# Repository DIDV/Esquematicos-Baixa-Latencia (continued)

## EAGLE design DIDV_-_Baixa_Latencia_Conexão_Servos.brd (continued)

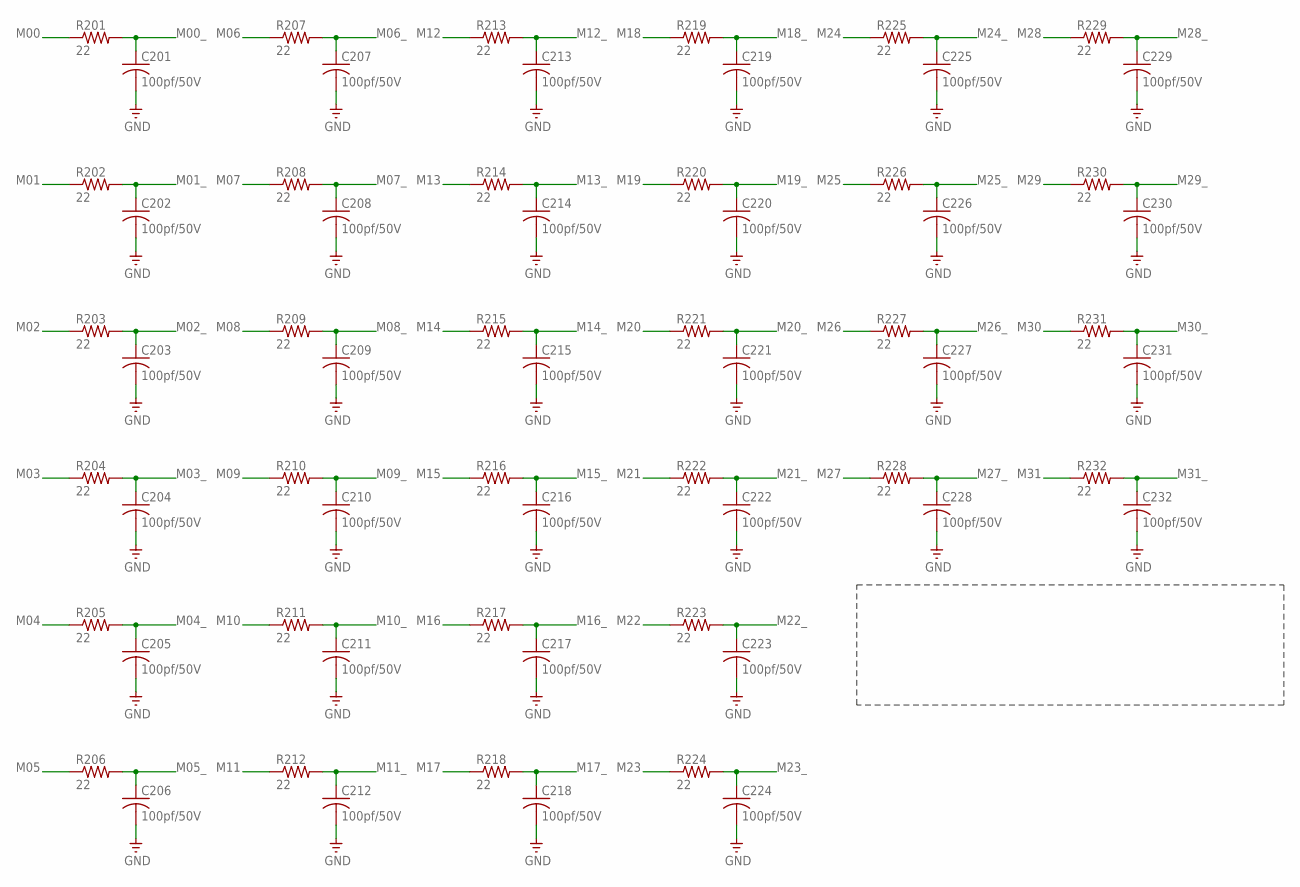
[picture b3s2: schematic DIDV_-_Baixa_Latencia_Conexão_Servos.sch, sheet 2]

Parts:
C201, C202, C203, C204, C205, C206, C207, C208, C209, C210, C211, C212, C213, C214, C215, C216, C217, C218, C219, C220, C221, C222, C223, C224, C225, C226, C227, C228, C229, C230, C231, C232: 100pf/50V; C0603
R201, R202, R203, R204, R205, R206, R207, R208, R209, R210, R211, R212, R213, R214, R215, R216, R217, R218, R219, R220, R221, R222, R223, R224, R225, R226, R227, R228, R229, R230, R231, R232: 22; R0603

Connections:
GND: C201.2, C202.2, C203.2, C204.2, C205.2, C206.2, C207.2, C208.2, C209.2, C210.2, C211.2, C212.2, C213.2, C214.2, C215.2, C216.2, C217.2, C218.2, C219.2, C220.2, C221.2, C222.2, C223.2, C224.2, C225.2, C226.2, C227.2, C228.2, C229.2, C230.2, C231.2, C232.2; also elsewhere on the board
M00: R201.1; also elsewhere on the board
M00_: C201.1, R201.2; also elsewhere on the board
M01: R202.1; also elsewhere on the board
M01_: C202.1, R202.2; also elsewhere on the board
M02: R203.1; also elsewhere on the board
M02_: C203.1, R203.2; also elsewhere on the board
M03: R204.1; also elsewhere on the board
M03_: C204.1, R204.2; also elsewhere on the board
M04: R205.1; also elsewhere on the board
M04_: C205.1, R205.2; also elsewhere on the board
M05: R206.1; also elsewhere on the board
M05_: C206.1, R206.2; also elsewhere on the board
M06: R207.1; also elsewhere on the board
M06_: C207.1, R207.2; also elsewhere on the board
M07: R208.1; also elsewhere on the board
M07_: C208.1, R208.2; also elsewhere on the board
M08: R209.1; also elsewhere on the board
M08_: C209.1, R209.2; also elsewhere on the board
M09: R210.1; also elsewhere on the board
M09_: C210.1, R210.2; also elsewhere on the board
M10: R211.1; also elsewhere on the board
M10_: C211.1, R211.2; also elsewhere on the board
M11: R212.1; also elsewhere on the board
M11_: C212.1, R212.2; also elsewhere on the board
M12: R213.1; also elsewhere on the board
M12_: C213.1, R213.2; also elsewhere on the board
M13: R214.1; also elsewhere on the board
M13_: C214.1, R214.2; also elsewhere on the board
M14: R215.1; also elsewhere on the board
M14_: C215.1, R215.2; also elsewhere on the board
M15: R216.1; also elsewhere on the board
M15_: C216.1, R216.2; also elsewhere on the board
M16: R217.1; also elsewhere on the board
M16_: C217.1, R217.2; also elsewhere on the board
M17: R218.1; also elsewhere on the board
M17_: C218.1, R218.2; also elsewhere on the board
M18: R219.1; also elsewhere on the board
M18_: C219.1, R219.2; also elsewhere on the board
M19: R220.1; also elsewhere on the board
M19_: C220.1, R220.2; also elsewhere on the board
M20: R221.1; also elsewhere on the board
M20_: C221.1, R221.2; also elsewhere on the board
M21: R222.1; also elsewhere on the board
M21_: C222.1, R222.2; also elsewhere on the board
M22: R223.1; also elsewhere on the board
M22_: C223.1, R223.2; also elsewhere on the board
M23: R224.1; also elsewhere on the board
M23_: C224.1, R224.2; also elsewhere on the board
M24: R225.1; also elsewhere on the board
M24_: C225.1, R225.2; also elsewhere on the board
M25: R226.1; also elsewhere on the board
M25_: C226.1, R226.2; also elsewhere on the board
M26: R227.1; also elsewhere on the board
M26_: C227.1, R227.2; also elsewhere on the board
M27: R228.1; also elsewhere on the board
M27_: C228.1, R228.2; also elsewhere on the board
M28: R229.1; also elsewhere on the board
M28_: C229.1, R229.2; also elsewhere on the board
M29: R230.1; also elsewhere on the board
M29_: C230.1, R230.2; also elsewhere on the board
M30: R231.1; also elsewhere on the board
M30_: C231.1, R231.2; also elsewhere on the board
M31: R232.1; also elsewhere on the board
M31_: C232.1, R232.2; also elsewhere on the board

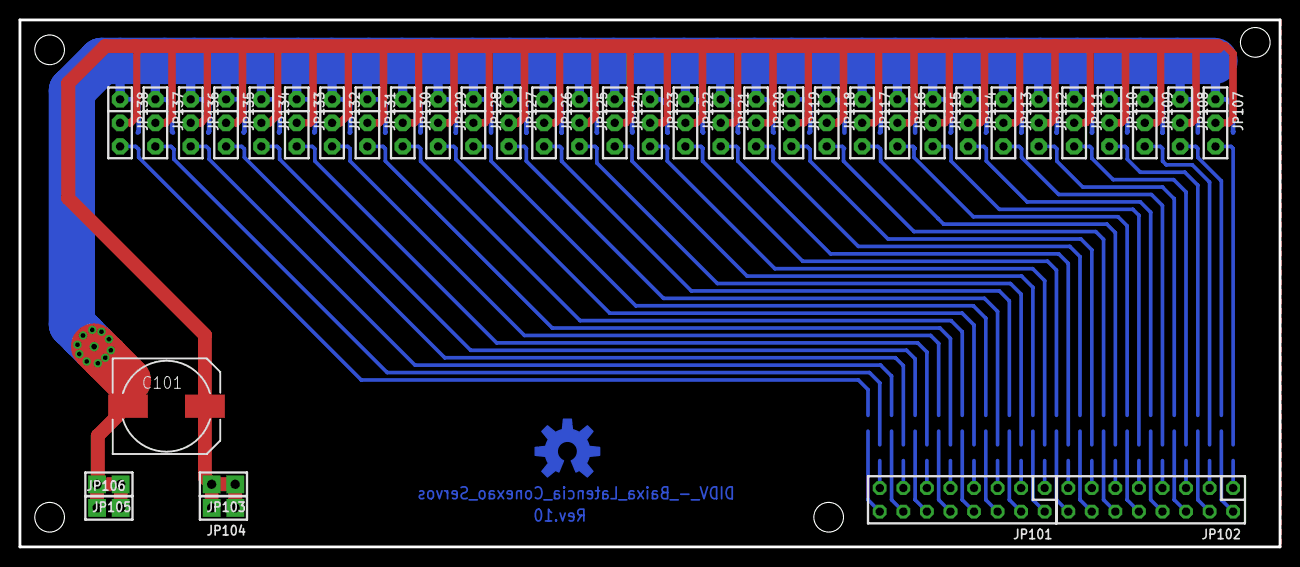
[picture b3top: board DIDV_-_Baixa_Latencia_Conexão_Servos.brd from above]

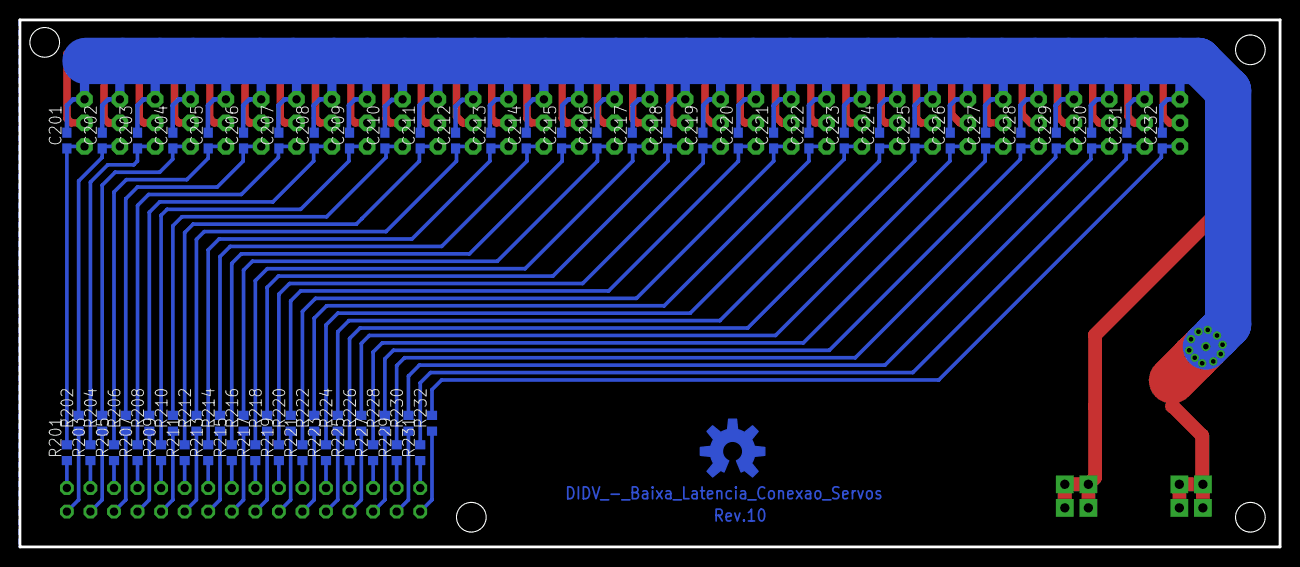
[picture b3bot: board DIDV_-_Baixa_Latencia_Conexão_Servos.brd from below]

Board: 2 copper layers, 135.9 x 56.8 mm, 104 parts (64 on the bottom side), 66 nets.

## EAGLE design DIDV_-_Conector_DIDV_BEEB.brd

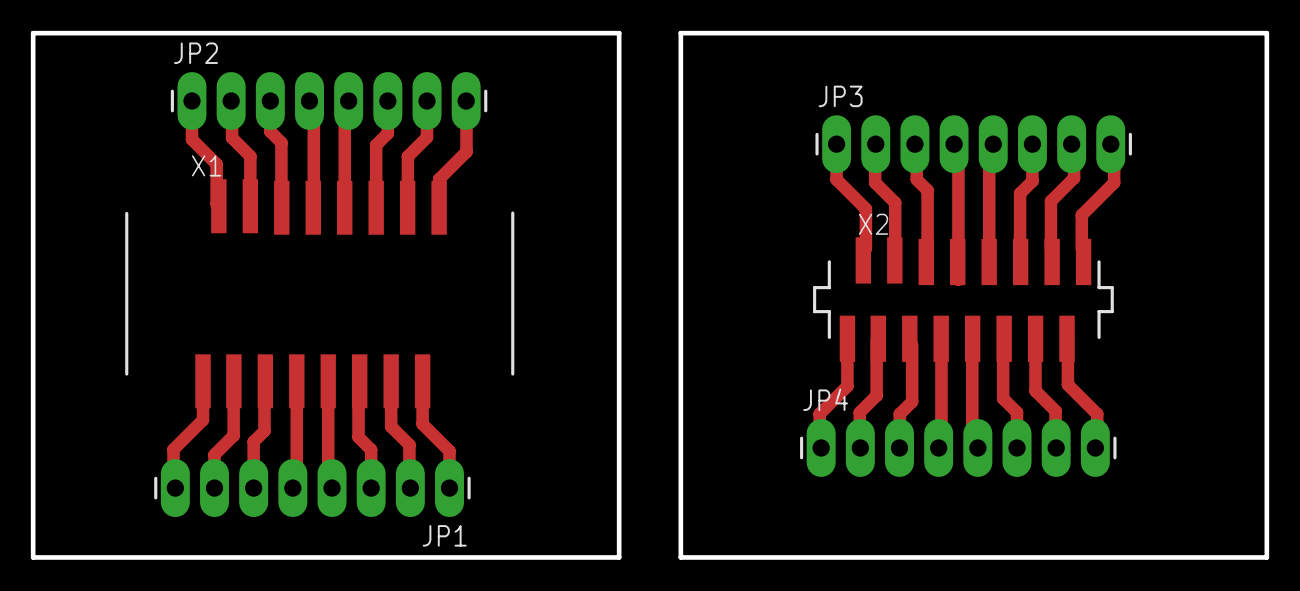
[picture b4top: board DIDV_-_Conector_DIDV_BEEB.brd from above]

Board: 2 copper layers, 80.0 x 34.0 mm, 6 parts (0 on the bottom side), 16 nets.

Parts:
JP1, JP2, JP3, JP4: 1X08_LONGPADS
X1, X2: SMDTOP16

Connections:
unnamed: JP1.8, X1.1
unnamed: JP1.1, X1.15
unnamed: JP1.7, X1.3
unnamed: JP1.6, X1.5
unnamed: JP1.5, X1.7
unnamed: JP1.2, X1.13
unnamed: JP1.3, X1.11
unnamed: JP1.4, X1.9
unnamed: JP2.7, X1.14
unnamed: JP2.6, X1.12
unnamed: JP2.5, X1.10
unnamed: JP2.2, X1.4
unnamed: JP2.3, X1.6
unnamed: JP2.4, X1.8
unnamed: JP2.1, X1.2
unnamed: JP2.8, X1.16

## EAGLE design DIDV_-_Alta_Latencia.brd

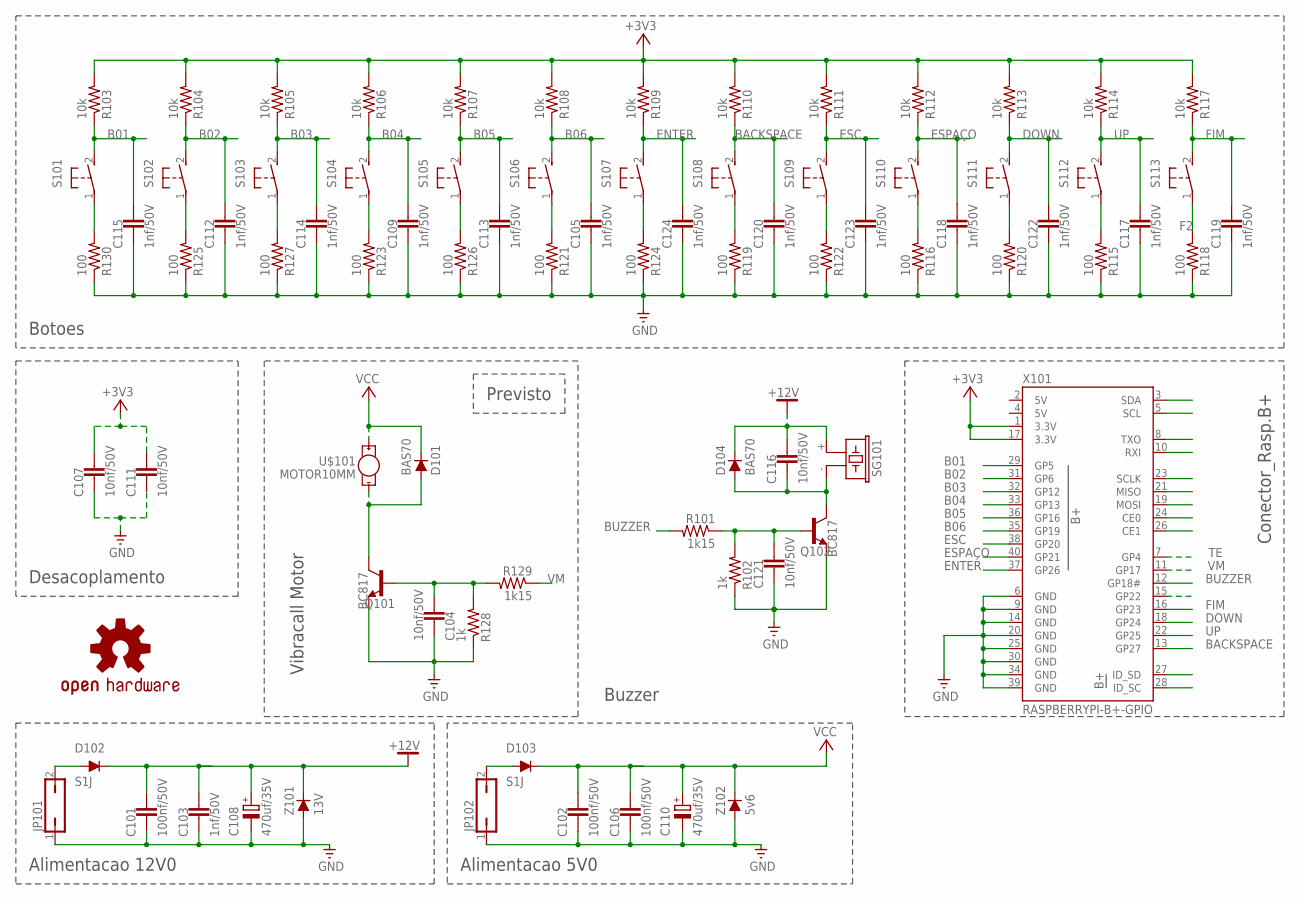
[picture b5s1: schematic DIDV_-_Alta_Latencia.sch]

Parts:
C101, C102, C106: 100nf/50V; C0805
C103: 1nf/50V; C0805
C104, C107, C111, C116, C121: 10nf/50V; C0603K
C105, C109, C112, C113, C114, C115, C117, C118, C119, C120, C122, C123, C124: 1nf/50V; C0603K
C108, C110: 470uf/35V; 140CLH-1014
D101, D104: BAS70; SOT23
D102, D103: S1J; DO214AC
JP101, JP102: JP1QY; JP1Y
LOGO101: OSHW-LOGOL; OSHW-LOGO-L
Q101, Q102: BC817; SOT23-BEC
R101, R129: 1k15; R0805
R102, R128: 1k; R0805
R103, R104, R105, R106, R107, R108, R109, R110, R111, R112, R113, R114, R117: 10k; R0603
R115, R116, R118, R119, R120, R121, R122, R123, R124, R125, R126, R127, R130: 100; R0603
S101, S102, S103, S104, S105, S106, S107, S108, S109, S110, S111, S112, S113: DTS-3
SG101: F/CM12P
U$101: MOTOR10MM; VIBE-MOTOR-10MM
X101: RASPBERRYPI-B+-GPIO; 2X20-SHROUDED
Z101: 13V; SOT23
Z102: 5v6; SOT23

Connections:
5V: X101.2 (5V), X101.4 (5V)
+3V3: C107.1, C111.1, R103.2, R104.2, R105.2, R106.2, R107.2, R108.2, R109.2, R110.2, R111.2, R112.2, R113.2, R114.2, R117.2, X101.1 (3.3V), X101.17 (3.3V)
+12V: C101.1, C103.1, C108.+, C116.1, D102.C, D104.3 (C), SG101.+ (1), Z101.3 (C)
B01: C115.1, R103.1, S101.2, X101.29 (GP5)
B02: C112.1, R104.1, S102.2, X101.31 (GP6)
B03: C114.1, R105.1, S103.2, X101.32 (GP12)
B04: C109.1, R106.1, S104.2, X101.33 (GP13)
B05: C113.1, R107.1, S105.2, X101.36 (GP16)
B06: C105.1, R108.1, S106.2, X101.35 (GP19)
BACKSPACE: C120.1, R110.1, S108.2, X101.13 (GP27)
BUZZER: R101.2, X101.12 (GP18#)
DOWN: C122.1, R113.1, S111.2, X101.18 (GP24)
ENTER: C124.1, R109.1, S107.2, X101.37 (GP26)
ESC: C123.1, R111.1, S109.2, X101.38 (GP20)
ESPAÇO: C118.1, R112.1, S110.2, X101.40 (GP21)
F2: R118.2, S113.1
FIM: C119.1, R117.1, S113.2, X101.16 (GP23)
GND: C101.2, C102.2, C103.2, C104.2, C105.2, C106.2, C107.2, C108.-, C109.2, C110.-, C111.2, C112.2, C113.2, C114.2, C115.2, C117.2, C118.2, C119.2, C120.2, C122.2, C123.2, C124.2, JP101.1, JP102.1, Q101.E, R115.1, R116.1, R118.1, R119.1, R120.1, R121.1, R122.1, R123.1, R124.1, R125.1, R126.1, R127.1, R128.1, R130.1, X101.6 (GND), X101.9 (GND), X101.14 (GND), X101.20 (GND), X101.25 (GND), X101.30 (GND), X101.34 (GND), X101.39 (GND), Z101.1 (A), Z102.1 (A)
unnamed: C116.2, D104.1 (A), Q102.C, SG101.- (2)
unnamed: C121.1, Q102.B, R101.1, R102.2
unnamed: R130.2, S101.1
unnamed: R121.2, S106.1
unnamed: R126.2, S105.1
unnamed: R123.2, S104.1
unnamed: R127.2, S103.1
unnamed: R125.2, S102.1
unnamed: R124.2, S107.1
unnamed: R115.2, S112.1
unnamed: R120.2, S111.1
unnamed: R116.2, S110.1
unnamed: R122.2, S109.1
unnamed: R119.2, S108.1
unnamed: C104.1, Q101.B, R128.2, R129.2
unnamed: D101.1 (A), Q101.C, U$101.-
unnamed: D102.A, JP101.2
unnamed: D103.A, JP102.2
unnamed: C121.2, Q102.E, R102.1
TE: X101.7 (GP4)
UP: C117.1, R114.1, S112.2, X101.22 (GP25)
VCC: C102.1, C106.1, C110.+, D101.3 (C), D103.C, U$101.+, Z102.3 (C)
VM: R129.1, X101.11 (GP17)

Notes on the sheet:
Buzzer
Botoes
Conector_Rasp.B+
Vibracall Motor
Previsto
Alimentacao 12V0
Alimentacao 5V0
Desacoplamento

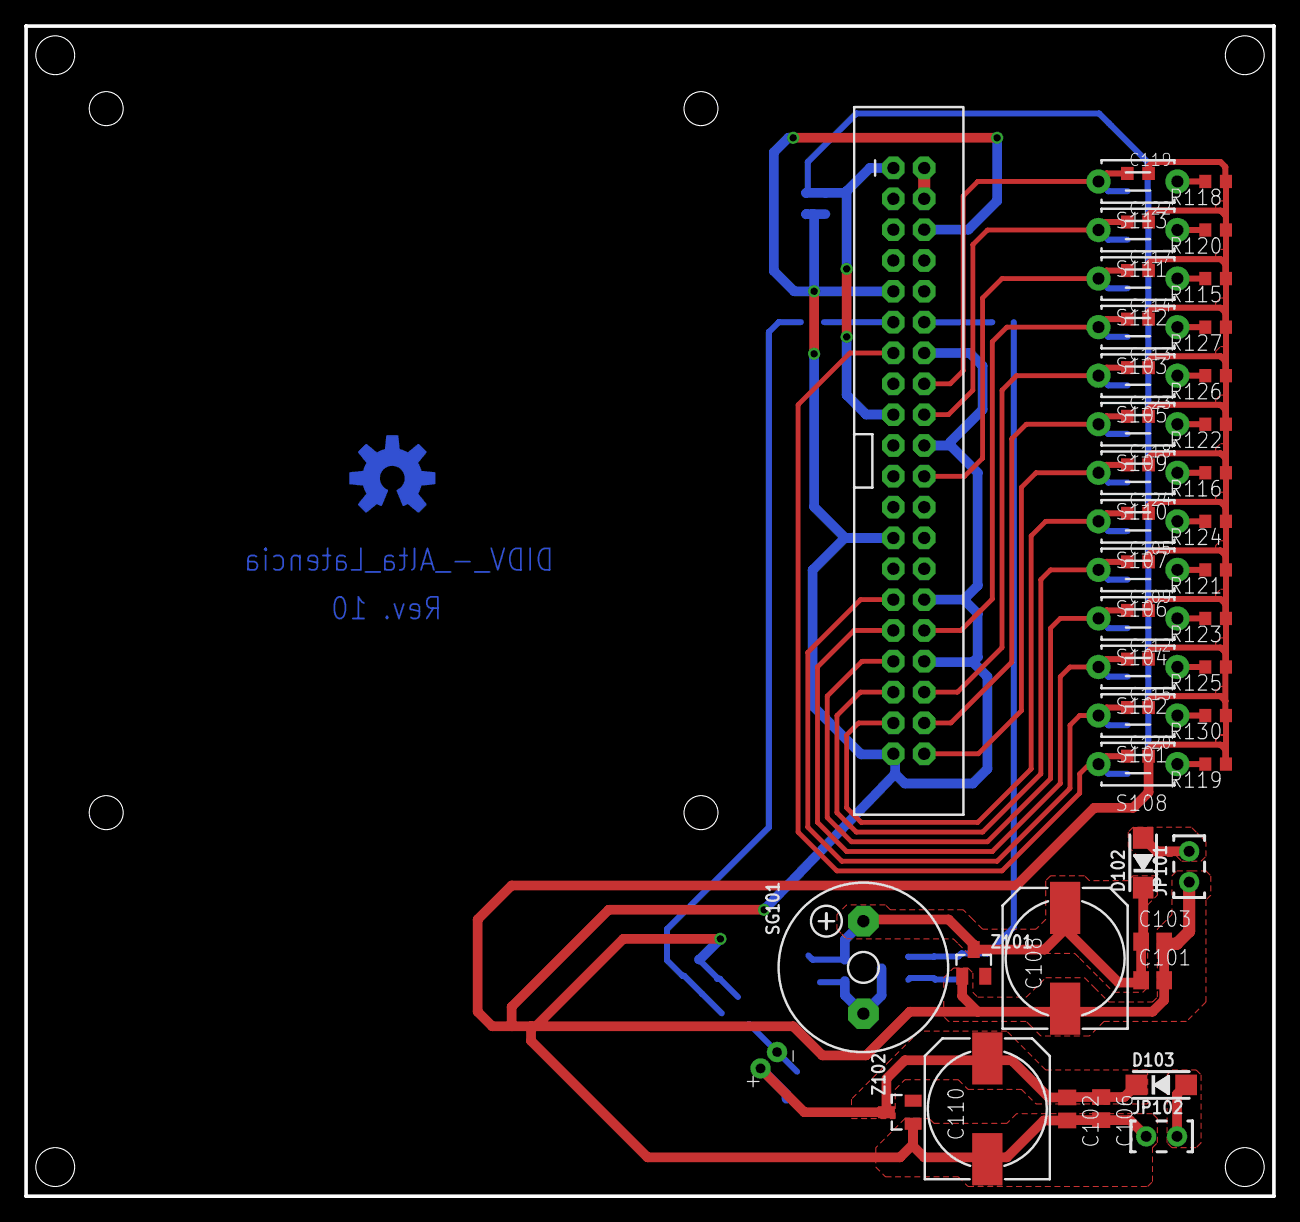
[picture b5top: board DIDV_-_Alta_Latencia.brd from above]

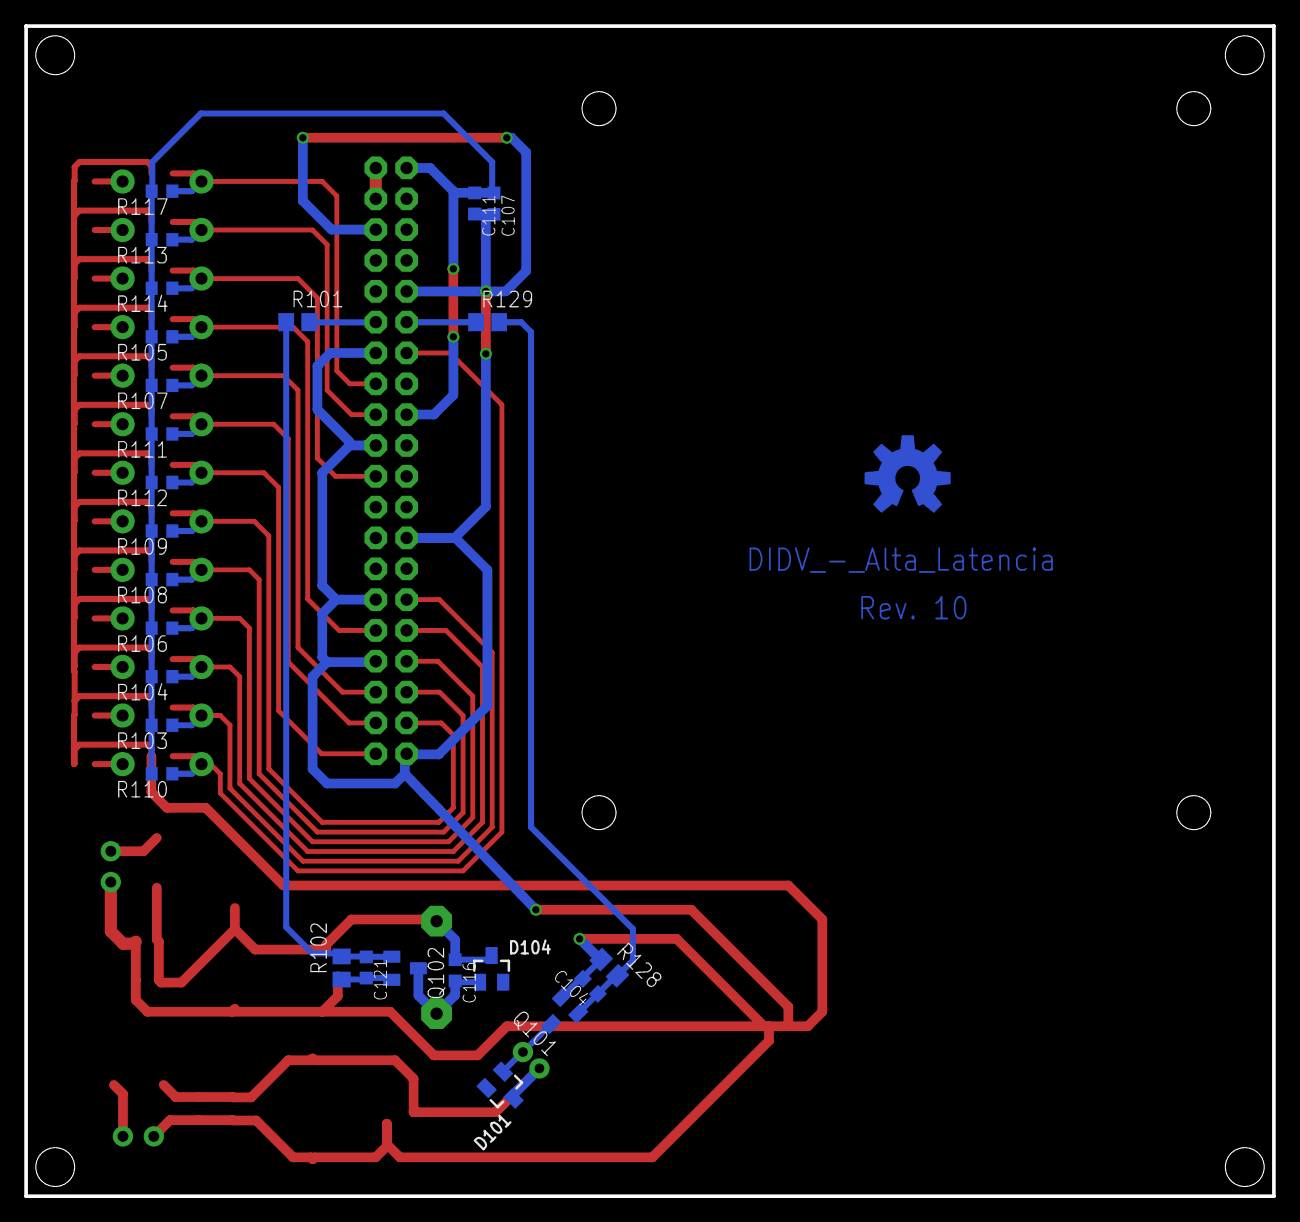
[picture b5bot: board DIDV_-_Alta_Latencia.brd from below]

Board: 2 copper layers, 102.8 x 96.4 mm, 81 parts (26 on the bottom side), 40 nets.

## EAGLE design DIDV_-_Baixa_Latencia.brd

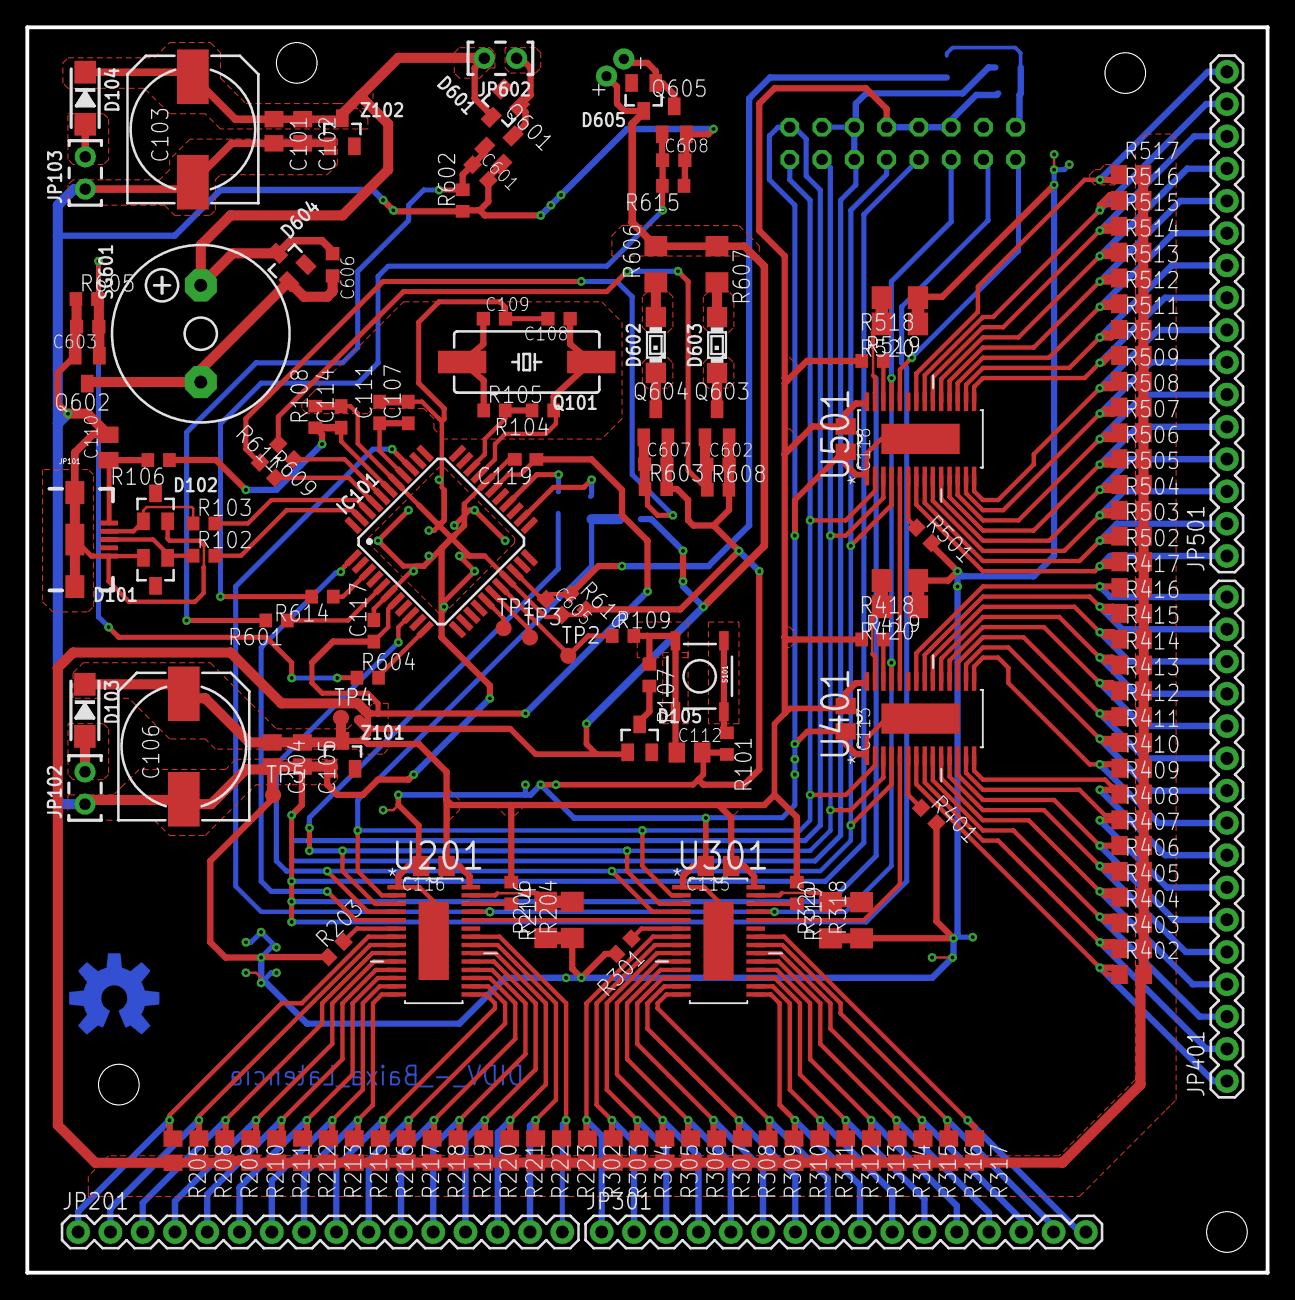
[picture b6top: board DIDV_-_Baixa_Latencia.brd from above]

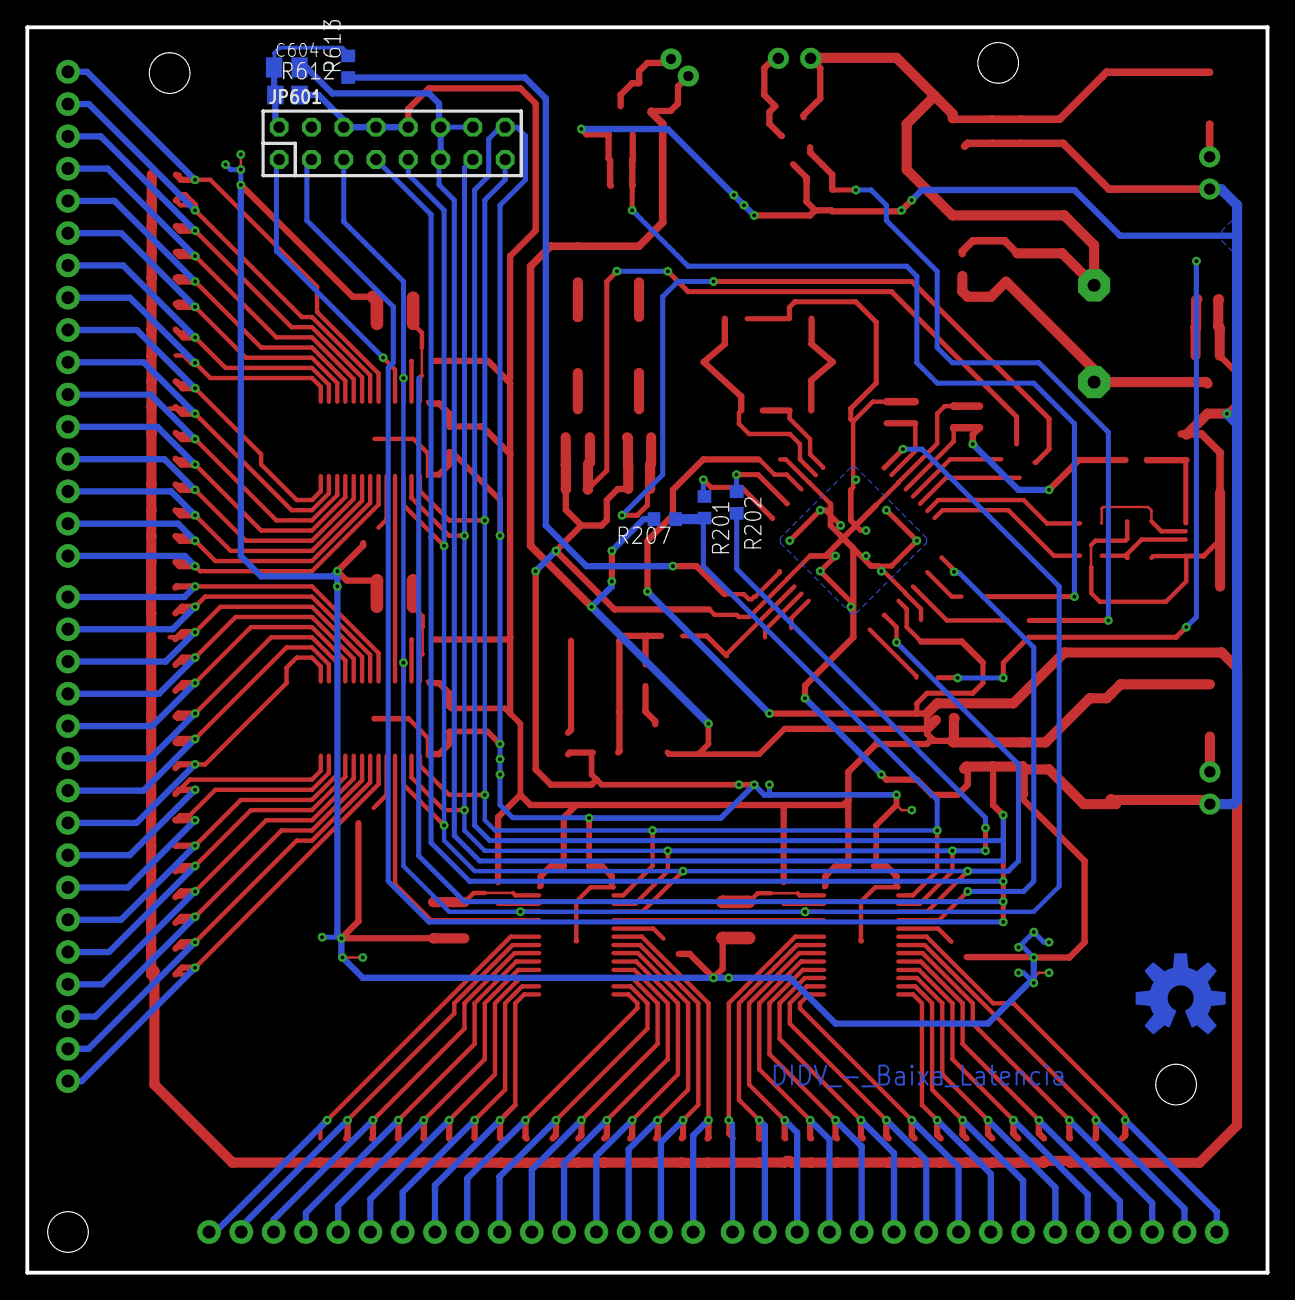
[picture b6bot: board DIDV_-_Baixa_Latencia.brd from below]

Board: 2 copper layers, 97.6 x 98.0 mm, 175 parts (7 on the bottom side), 127 nets.

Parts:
C101, C102, C104, C105: 100nf/50V; C0805
C103, C106: 470uf/35V; 140CLH-1014
C107, C111: 100n; C0603
C108, C109: 15p; C0603K
C110, C113, C115, C116, C118, C604: 10n; C0805K
C112: 1u; C0805K
C114, C117, C119: 10n; C0603
C601, C603, C606, C608: 10nf/50V; C0603K
C602, C605, C607: 10n; C0603K
D101, D102: ESDAXXL; SOT23
D103, D104: S1J; DO214AC
D105: BAS21; SOT23@1
D601, D604, D605: BAS70; SOT23
D602, D603: MINI-TOPLED-SANTANA
IC101: PIC18F4550_TQFP44; TQFP44
JP101: USB-B-MICRO-SMD_V03
JP102, JP103: JP1Y
JP201, JP301, JP401, JP501: M16PTH; 1X16
JP601: JP8Q
JP602: Rele_40A; JP1Y
LOGO101: OSHW-LOGOL; OSHW-LOGO-L
Q101: SM49
Q601, Q602, Q603, Q604, Q605: BC817; SOT23-BEC
R101, R105: 100; R0603
R102, R103: 22R; R0603
R104: 1M; R0603
R106, R107, R203, R214, R301, R319, R401, R419, R501, R519, R613: 10k; R0603
R108, R610: 100k; R0603
R109: 1k5; R0603
R201, R202: 22; R0603
R204, R318, R418, R518: RX; R1206
R205, R208, R209, R210, R211, R212, R213, R215, R216, R217, R218, R219, R220, R221, R222, R223, R302, R303, R304, R305, R306, R307, R308, R309, R310, R311, R312, R313, R314, R315, R316, R317, R402, R403, R404, R405, R406, R407, R408, R409, R410, R411, R412, R413, R414, R415, R416, R417, R502, R503, R504, R505, R506, R507, R508, R509, R510, R511, R512, R513, R514, R515, R516, R517: R0805
R206, R320, R420, R520: R1206
R207: R0603
R601, R603, R604, R608, R614: 2k; R0603
R602, R605, R615: 1k3; R0603
R606, R607: 110; R1206
R609, R611: 3k; R0603
R612: 100k; R0805
S101: TACTILE-SWITCH-SMD
SG601: F/CM12P
TP1, TP2, TP3, TP4, TP5: TPB1,27; B1,27
U201, U301, U401, U501: TLC5940QPWPREP; SOP65P640X120-29N
U$601: MOTOR10MM; VIBE-MOTOR-10MM
Z101: 5v6; SOT23
Z102: 12V6; SOT23

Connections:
+12V: C101.1, C102.1, C103.+, C606.1, D104.C, D601.3, D604.3, JP602.2, SG601.+, Z102.3
BLANK: IC101.24, R201.1
BLANK_: JP601.15, R201.2, R207.1, U201.2, U301.2, U401.2, U501.2
BUZZER: IC101.11, R604.2
D+: IC101.43, R102.2
D-: IC101.42, R103.2
EXPA: JP601.1, U501.24
GND: C101.2, C102.2, C103.-, C104.2, C105.2, C106.-, C107.2, C108.2, C109.2, C110.2, C111.2, C112.2, C113.2, C114.2, C115.2, C116.2, C117.2, C118.2, C119.2, C601.2, C602.2, C603.2, C604.2, C605.2, C607.2, C608.2, D101.2, D102.2, IC101.6, IC101.19, IC101.29, IC101.38, JP101.GND1, JP101.SHIELD1, JP101.SHIELD2, JP101.SHIELD3, JP102.1, JP103.1, JP601.3, JP601.7, JP601.11, JP601.12, JP601.14, JP601.16, Q601.E, Q602.E, Q603.E, Q604.E, Q605.E, R101.2, R108.2, R203.1, R204.1, R206.1, R301.2, R318.1, R320.1, R401.2, R418.1, R420.1, R501.2, R518.1, R520.1, R602.1, R603.2, R605.1, R608.2, R610.2, R615.1, TP5.TP, U201.1, U201.29, U301.1, U301.29, U401.1, U401.29, U501.1, U501.29, Z101.1, Z102.1
GSCLK: IC101.36, JP601.5, U201.25, U301.25, U401.25, U501.25
IR201: R204.2, R206.2, U201.27
IR301: R318.2, R320.2, U301.27
IR401: R418.2, R420.2, U401.27
IR501: R518.2, R520.2, U501.27
M00: JP201.1, R205.1, U201.7
M01: JP201.2, R208.1, U201.8
M02: JP201.3, R209.1, U201.9
M03: JP201.4, R210.1, U201.10
M04: JP201.5, R211.1, U201.11
M05: JP201.6, R212.1, U201.12
M06: JP201.7, R213.1, U201.13
M07: JP201.8, R215.1, U201.14
M08: JP201.9, R216.1, U201.15
M09: JP201.10, R217.1, U201.16
M10: JP201.11, R218.1, U201.17
M11: JP201.12, R219.1, U201.18
M12: JP201.13, R220.1, U201.19
M13: JP201.14, R221.1, U201.20
M14: JP201.15, R222.1, U201.21
M15: JP201.16, R223.1, U201.22
M16: JP301.1, R302.1, U301.7
M17: JP301.2, R303.1, U301.8
M18: JP301.3, R304.1, U301.9
M19: JP301.4, R305.1, U301.10
M20: JP301.5, R306.1, U301.11
M21: JP301.6, R307.1, U301.12
M22: JP301.7, R308.1, U301.13
M23: JP301.8, R309.1, U301.14
M24: JP301.9, R310.1, U301.15
M25: JP301.10, R311.1, U301.16
M26: JP301.11, R312.1, U301.17
M27: JP301.12, R313.1, U301.18
M28: JP301.13, R314.1, U301.19
M29: JP301.14, R315.1, U301.20
M30: JP301.15, R316.1, U301.21
M31: JP301.16, R317.1, U301.22
M32: JP401.1, R402.1, U401.7
M33: JP401.2, R403.1, U401.8
M34: JP401.3, R404.1, U401.9
M35: JP401.4, R405.1, U401.10
M36: JP401.5, R406.1, U401.11
M37: JP401.6, R407.1, U401.12
M38: JP401.7, R408.1, U401.13
M39: JP401.8, R409.1, U401.14
M40: JP401.9, R410.1, U401.15
M41: JP401.10, R411.1, U401.16
M42: JP401.11, R412.1, U401.17
M43: JP401.12, R413.1, U401.18
M44: JP401.13, R414.1, U401.19
M45: JP401.14, R415.1, U401.20
M46: JP401.15, R416.1, U401.21
M47: JP401.16, R417.1, U401.22
M48: JP501.1, R502.1, U501.7
M49: JP501.2, R503.1, U501.8
M50: JP501.3, R504.1, U501.9
M51: JP501.4, R505.1, U501.10
M52: JP501.5, R506.1, U501.11
M53: JP501.6, R507.1, U501.12
M54: JP501.7, R508.1, U501.13
M55: JP501.8, R509.1, U501.14
M56: JP501.9, R510.1, U501.15
M57: JP501.10, R511.1, U501.16
M58: JP501.11, R512.1, U501.17
M59: JP501.12, R513.1, U501.18
M60: JP501.13, R514.1, U501.19
M61: JP501.14, R515.1, U501.20
M62: JP501.15, R516.1, U501.21
M63: JP501.16, R517.1, U501.22
MCLR: IC101.18, R109.1, TP2.TP
unnamed: D105.3, R107.2
unnamed: D102.1, JP101.D-1, R103.1
unnamed: D101.1, JP101.D+1, R102.1
unnamed: C606.2, D604.1, Q602.C, SG601.-
unnamed: C109.1, Q101.2, R105.1
unnamed: D602.A, R606.1
unnamed: C603.1, Q602.B, R604.1, R605.2
unnamed: R401.1, U401.6
unnamed: R501.1, U501.6
unnamed: D603.A, R607.2
unnamed: D104.A, JP103.2
unnamed: D602.C, Q604.C
unnamed: D103.A, JP102.2
unnamed: D603.C, Q603.C
unnamed: C602.1, Q603.B, R608.1, R611.2
unnamed: C607.1, Q604.B, R603.1, R609.1
unnamed: C608.1, Q605.B, R614.2, R615.2
unnamed: R203.2, U201.6
unnamed: D605.1, Q605.C, U$601.-
unnamed: R319.2, U301.26
unnamed: R101.1, S101.1, S101.2
unnamed: D601.1, JP602.1, Q601.C
unnamed: C601.1, Q601.B, R601.2, R602.2
unnamed: R419.2, U401.26
unnamed: R519.2, U501.26
unnamed: R214.2, U201.26
OSC1: C108.1, IC101.30, Q101.1, R104.1
OSC2: IC101.31, R104.2, R105.2
PGC: IC101.16, TP1.TP
PGD: IC101.17, TP3.TP
RA: C604.1, JP601.2, R612.1, R613.2
RA_2: C605.1, IC101.20, R610.1, R613.1
SCLK: IC101.9, JP601.9, U201.4, U301.4, U401.4, U501.4
SIN: IC101.1, U201.5
SOUT201: U201.24, U301.5
SOUT301: U301.24, U401.5
SOUT401: U401.24, U501.5
TM_EN: IC101.5, R601.1
USBCON: IC101.41, R609.2
USBTXRX: IC101.40, R611.1
USB_IN: C114.1, IC101.39, R106.1, R108.1
U_MCLR: C112.1, R107.1, R109.2, S101.3, S101.4
VCC: C104.1, C105.1, C106.+, C113.1, C115.1, C116.1, C117.1, C118.1, C119.1, D103.C, D105.1, D605.3, IC101.7, IC101.28, JP601.6, JP601.8, JP601.10, R205.2, R207.2, R208.2, R209.2, R210.2, R211.2, R212.2, R213.2, R214.1, R215.2, R216.2, R217.2, R218.2, R219.2, R220.2, R221.2, R222.2, R223.2, R302.2, R303.2, R304.2, R305.2, R306.2, R307.2, R308.2, R309.2, R310.2, R311.2, R312.2, R313.2, R314.2, R315.2, R316.2, R317.2, R319.1, R402.2, R403.2, R404.2, R405.2, R406.2, R407.2, R408.2, R409.2, R410.2, R411.2, R412.2, R413.2, R414.2, R415.2, R416.2, R417.2, R419.1, R502.2, R503.2, R504.2, R505.2, R506.2, R507.2, R508.2, R509.2, R510.2, R511.2, R512.2, R513.2, R514.2, R515.2, R516.2, R517.2, R519.1, R606.2, R607.1, R612.2, TP4.TP, U201.28, U301.28, U401.28, U501.28, U$601.+, Z101.3
VM: IC101.3, R614.1
VPRG_: R301.1, U301.6
VUSB: C110.1, JP101.VBUS1, R106.2
VUSB_: C107.1, C111.1, IC101.37
XLAT: IC101.26, R202.1
XLAT_: JP601.13, R202.2, U201.3, U301.3, U401.3, U501.3

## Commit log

2014-10-02 - Criação dos arquivos primários (esquemático); - BOM List, a primeira revisão; - Cálculos iniciais.
2014-10-02 - Inclusão do circuito de buzzer; - Correção e prevenção contra ruídos nas linhas comunicação;
2014-10-03 Better README.md
2014-10-06 Rev4 - Adição do circuito de Alta Latência - Previsão de conexão de módulos de expansão - Correção de falhas e previsão de melhorias com relação a estabilidade do sistema - Definição dos valores inic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
2014-10-09 Rev005
    - Inclusão de resistor série na linha do oscilador;
    - Nomenclatura correta dos componentes e nets;
    - Correção dos valores dos componentes.
2014-10-19 Readequação da Licença Para o uso de hardware, a licença 'SolderPad 0.51' é mais indicada. Licença baseada na Apache 2.0, versão completa pode ser encontrada em: http://solderpad.org/licenses/SHL-0.5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
2015-01-15 Retirada dos arquivos referentes a versão 5, pois, devido a grande quantidade de alterações não refletem mais a realidade do projeto. sendo assim, a partir da revisão 6 partiremos para o desenvolvime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
2015-01-15 Revisão 7:
    - Alterações necessárias para adequação às necessidades dos exemplos de controle que temos.
    - Revisão da forma de filtragem de sinais digitais
    - Algumas nomenclaturas ainda estão erradas, deverão ser corrigidas com o andamento da implementação.
2015-02-16 Revisão 8:
    - Add Circuito Buck
    - Alterações funcionais
    - Inserção dos primeiros boards
2015-02-27 Revisão 9
    - Corrigidos algumas falhas de ligação
    - Implementação com VPRG dos TLCs via Hardware
    - Inserção do cálculo do Riref
    Obs. Se somente a criação de boards, não será incrementado. No caso, se criado um board novo board vou subir para 9.1 e assim por diante.
2015-04-21 Revisão 10
    Revisão representa o estado final do projeto, alterações agora somente referentes a valores de componentes e adaptações se e somente se não existir a possibilidade de manobras via software.
    Placas nas dimensões e condições as quais foram submetidas a cotação para confecção em local especializado.
